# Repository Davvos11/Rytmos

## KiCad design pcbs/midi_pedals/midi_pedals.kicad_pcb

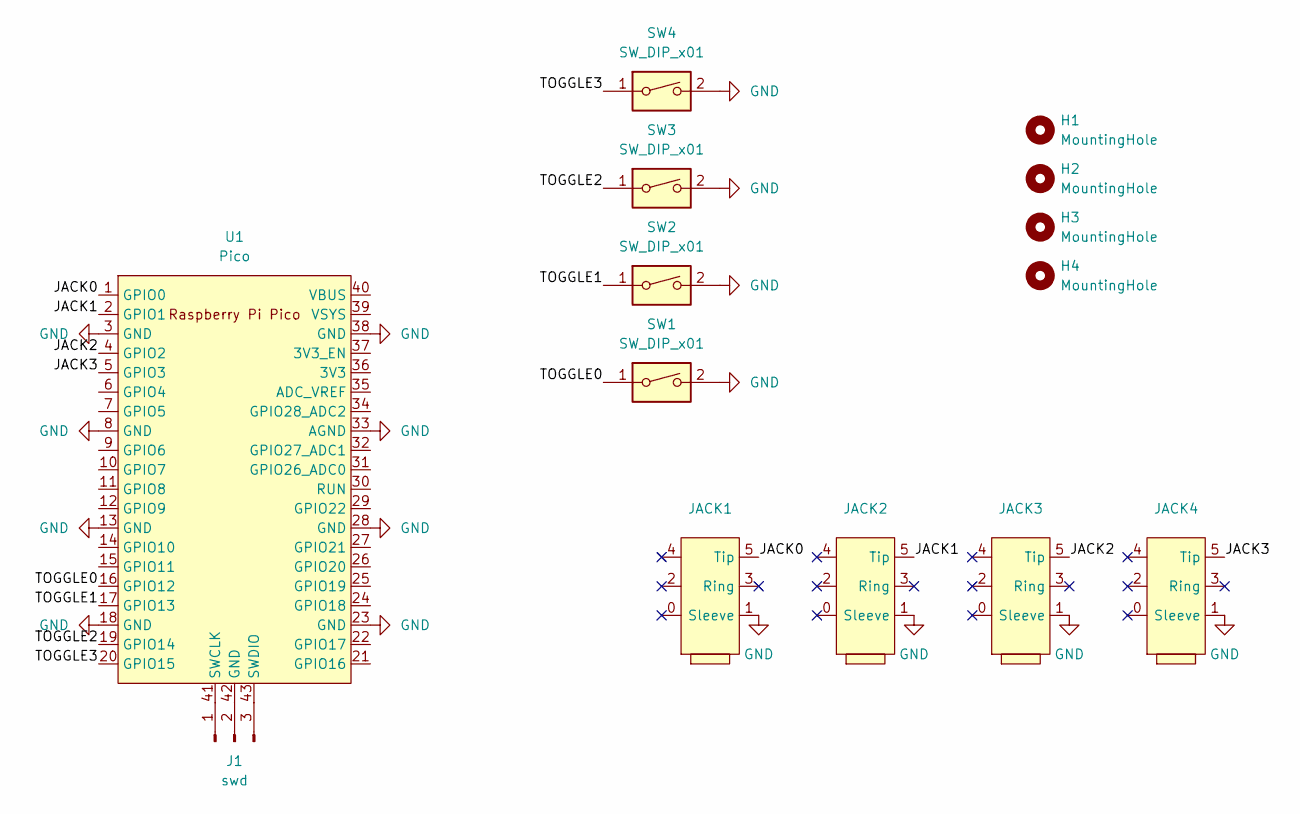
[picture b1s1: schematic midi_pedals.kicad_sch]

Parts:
H1, H2, H3, H4: MountingHole; MountingHole_3.2mm_M3
J1: swd; PinSocket_1x03_P2.54mm_Vertical
JACK1, JACK2, JACK3, JACK4: Jack_6.3mm
SW1, SW2, SW3, SW4: SW_DIP_x01; PinSocket_1x03_P2.54mm_Vertical
U1: Pico; RPi_Pico_SMD_TH

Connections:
/JACK0: JACK1.5 (Tip), U1.1 (GPIO0)
/JACK1: JACK2.5 (Tip), U1.2 (GPIO1)
/JACK2: JACK3.5 (Tip), U1.4 (GPIO2)
/JACK3: JACK4.5 (Tip), U1.5 (GPIO3)
/TOGGLE0: SW1.1, U1.16 (GPIO12)
/TOGGLE1: SW2.1, U1.17 (GPIO13)
/TOGGLE2: SW3.1, U1.19 (GPIO14)
/TOGGLE3: SW4.1, U1.20 (GPIO15)
GND: JACK1.1 (Sleeve), JACK2.1 (Sleeve), JACK3.1 (Sleeve), JACK4.1 (Sleeve), SW1.2, SW2.2, SW3.2, SW4.2, U1.3 (GND), U1.8 (GND), U1.13 (GND), U1.18 (GND), U1.23 (GND), U1.28 (GND), U1.33 (AGND), U1.38 (GND)
unnamed: J1.1, U1.41 (SWCLK)
unnamed: J1.2, U1.42 (GND)
unnamed: J1.3, U1.43 (SWDIO)

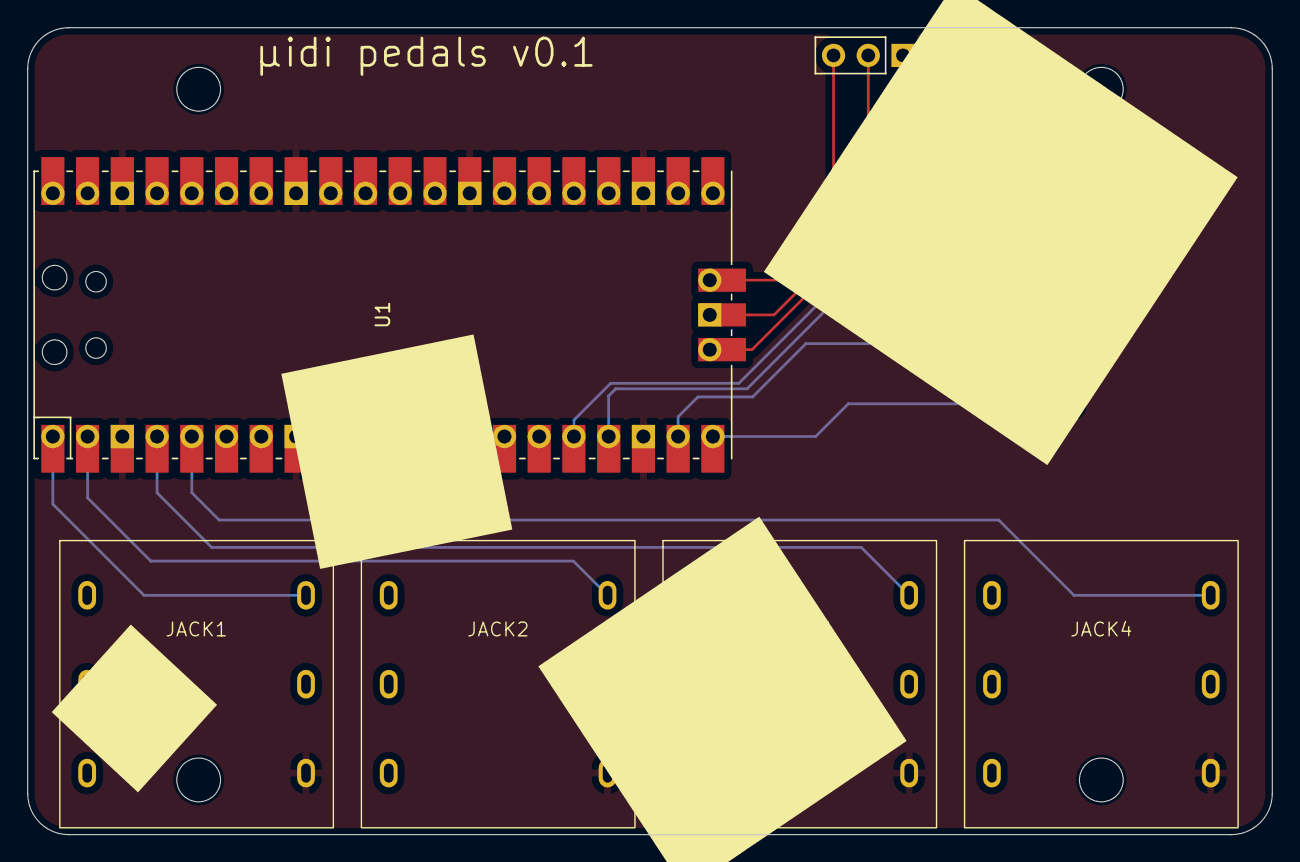
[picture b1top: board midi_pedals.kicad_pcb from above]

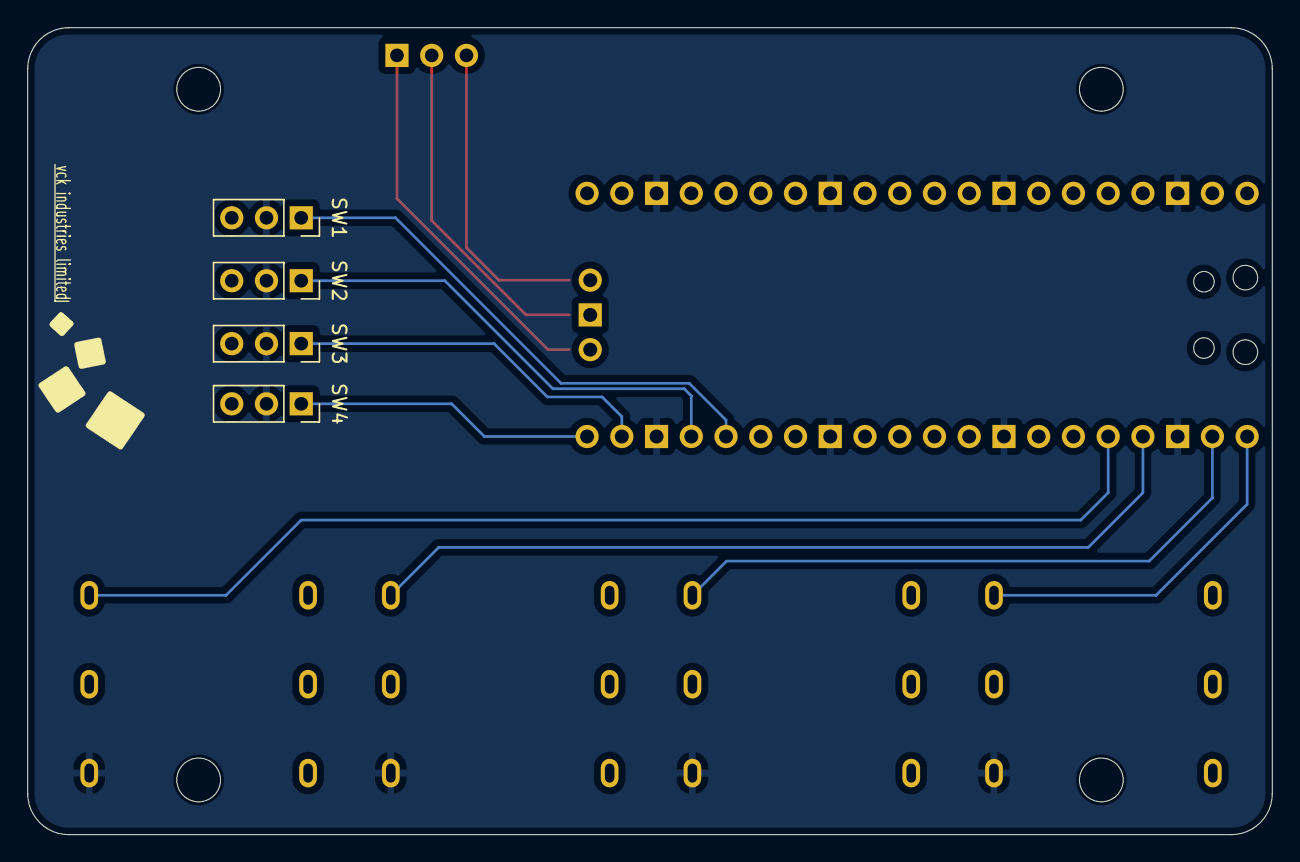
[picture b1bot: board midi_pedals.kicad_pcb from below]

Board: 2 copper layers, 91.0 x 59.0 mm, 14 parts (4 on the bottom side), 12 nets.

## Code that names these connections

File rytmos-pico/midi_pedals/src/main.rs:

#![no_std]
#![no_main]

#[link_section = ".boot2"]
#[no_mangle]
#[used]
pub static BOOT2_FIRMWARE: [u8; 256] = rp2040_boot2::BOOT_LOADER_W25Q080;

use common::debouncer::Debouncer;
use defmt::*;
use defmt_rtt as _;
use embedded_hal::digital::v2::InputPin;
use embedded_hal::digital::v2::OutputPin;
use heapless::Vec;
use itertools::izip;
use panic_probe as _;
use rp_pico::hal::timer::Instant;
use rp_pico::hal::Timer;
use rp_pico::{
    entry,
    hal::{
        clocks::{init_clocks_and_plls, Clock},
        gpio::{self, FunctionSio, Pin, PullUp, SioInput},
        sio::Sio,
        usb::UsbBus,
        Watchdog,
    },
    pac,
};
use usb_device::device::StringDescriptors;
use usb_device::{
    bus::UsbBusAllocator,
    device::{UsbDeviceBuilder, UsbVidPid},
};
use usbd_midi::message::{ControlFunction, U7};
use usbd_midi::CableNumber;
use usbd_midi::Message::ControlChange;
use usbd_midi::{message::Channel, UsbMidiClass};

const PEDALS: usize = 4;
const CC_BANK_A: u8 = 1;
const CC_BANK_B: u8 = 64;

#[entry]
fn main() -> ! {
    let mut pac = pac::Peripherals::take().unwrap();
    let core = pac::CorePeripherals::take().unwrap();
    let sio = Sio::new(pac.SIO);

    let mut watchdog = Watchdog::new(pac.WATCHDOG);
    let clocks = init_clocks_and_plls(
        rp_pico::XOSC_CRYSTAL_FREQ,
        pac.XOSC,
        pac.CLOCKS,
        pac.PLL_SYS,
        pac.PLL_USB,
        &mut pac.RESETS,
        &mut watchdog,
    )
    .ok()
    .unwrap();

    let mut delay = cortex_m::delay::Delay::new(core.SYST, clocks.system_clock.freq().to_Hz());

    let timer = Timer::new(pac.TIMER, &mut pac.RESETS, &clocks);

    let pins = gpio::Pins::new(
        pac.IO_BANK0,
        pac.PADS_BANK0,
        sio.gpio_bank0,
        &mut pac.RESETS,
    );

    info!("Creating usb devices.");

    let usb_bus = UsbBusAllocator::new(UsbBus::new(
        pac.USBCTRL_REGS,
        pac.USBCTRL_DPRAM,
        clocks.usb_clock,
        true,
        &mut pac.RESETS,
    ));

    let mut led_pin = pins.gpio25.into_push_pull_output();

    let pedal_pins: [Pin<_, FunctionSio<SioInput>, PullUp>; PEDALS] = [
        pins.gpio0.reconfigure().into_dyn_pin(),
        pins.gpio1.reconfigure().into_dyn_pin(),
        pins.gpio2.reconfigure().into_dyn_pin(),
        pins.gpio3.reconfigure().into_dyn_pin(),
    ];
    let mut pedal_debouncers: Vec<_, PEDALS> =
        pedal_pins.iter().map(|_| Debouncer::new(1000)).collect();

    let switch1: Pin<_, FunctionSio<SioInput>, PullUp> = pins.gpio12.reconfigure();
    let switch2: Pin<_, FunctionSio<SioInput>, PullUp> = pins.gpio13.reconfigure();
    let mut switch1_deb = Debouncer::new(1000);
    let mut switch2_deb = Debouncer::new(1000);

    let control_changes_a = create_ccs(CC_BANK_A);
    let control_changes_b = create_ccs(CC_BANK_B);

    led_pin.set_high().unwrap();

    let mut midi = UsbMidiClass::new(&usb_bus, 1, 0).unwrap();

    let mut usb_dev = UsbDeviceBuilder::new(&usb_bus, UsbVidPid(0xabc9, 0xee0))
        .device_class(0)
        .device_sub_class(0)
        .strings(&[StringDescriptors::default()
            .manufacturer("de vck")
            .product("midi pedals lmao")
            .serial_number("0")])
        .unwrap()
        .build();

    info!("usb device is created");

    let mut control_changes = if switch1.is_high().unwrap() {
        info!(
            "Starting using bank A (switch 1: {})",
            switch1.is_high().unwrap()
        );
        &control_changes_a
    } else {
        info!(
            "Starting using bank B (switch 1: {})",
            switch1.is_high().unwrap()
        );
        &control_changes_b
    };
    let mut double_cancellation = switch2.is_high().unwrap();
    info!(
        "Starting with double-press cancellation = {}",
        double_cancellation
    );
    // Create counters for each pedal (0: last time pedal up, 1: last time pedal down)
    let mut last_presses: Vec<_, PEDALS> =
        pedal_pins.iter().map(|_| (Instant::from_ticks(0), Instant::from_ticks(0))).collect();
    let mut pressed = pedal_pins.iter().filter(|p| p.is_high().unwrap()).count();

    loop {
        // Poll USB device to keep connection alive
        usb_dev.poll(&mut [&mut midi]);

        switch1_deb.update(switch1.is_high().unwrap());
        switch2_deb.update(switch2.is_high().unwrap());

        // Determine the CC values based on the switch setting
        if switch1_deb.stable_rising_edge() {
            debug!("Switching to bank A");
            // Send pedal off to all B channels (when switching)
            for cc in &control_changes_b {
                send_midi_cc(&mut midi, cc, U7::MIN).ok();
                delay.delay_ms(1);
            }
            // Set current channels to A
            control_changes = &control_changes_a;
        } else if switch1_deb.stable_falling_edge() {
            debug!("Switching to bank B");
            for cc in &control_changes_a {
                send_midi_cc(&mut midi, cc, U7::MIN).ok();
                delay.delay_ms(1);
            }
            // Set current channels to B
            control_changes = &control_changes_b;
        }

        // Determine if we double-press-cancellation is enabled
        if switch2_deb.stable_rising_edge() {
            debug!("Enabling double-press cancellation");
            double_cancellation = true;
        } else if switch2_deb.stable_falling_edge() {
            debug!("Disabling double-press cancellation");
            double_cancellation = false;
        }

        for (pin, debouncer, cc, last_pressed) in izip!(
            &pedal_pins,
            &mut pedal_debouncers,
            control_changes,
            &mut last_presses
        ) {
            debouncer.update(pin.is_high().unwrap());
            let mut up = false;
            let mut down = false;

            if debouncer.stable_falling_edge() {
                down = true;
                debug!("{} down (MIDI {})", pin.id().num, u8::from(cc.0.clone()));
                pressed += 1;
            }

            if debouncer.stable_rising_edge() {
                up = true;
                debug!("{} up (MIDI {})", pin.id().num, u8::from(cc.0.clone()));
                pressed = pressed.saturating_sub(1);
            }
            
            if up || down {
                // Determine time since last up or down event and determine if we should cancel
                let elapsed = if up {
                    timer.get_counter().checked_duration_since(last_pressed.0)
                } else {
                    timer.get_counter().checked_duration_since(last_pressed.1)
                };
                let should_cancel = elapsed.map(|e| e.to_millis() <= 500).unwrap_or(false);
                if double_cancellation && should_cancel {
                    debug!("Cancelled sending midi ({:?} ms since last press)", elapsed.map(|e| e.to_millis()));
                }
                // Send MIDI signal (or cancel)
                if !double_cancellation || !should_cancel {
                    let value = if up {U7::MIN} else {U7::MAX};
                    send_midi_cc(&mut midi, cc, value).ok();
                }
                // Update timers
                if up {
                    last_pressed.0 = timer.get_counter();
                } else {
                    last_pressed.1 = timer.get_counter();
                }
            }
        }

        if pressed > 0 {
            led_pin.set_low().ok();
        } else {
            led_pin.set_high().ok();
        }
    }
}

fn send_midi_cc(
    midi: &mut UsbMidiClass<UsbBus>,
    cc: &ControlFunction,
    value: U7,
) -> usb_device::Result<usize> {
    midi.send_packet(
        ControlChange(Channel::Channel1, cc.clone(), value).into_packet(CableNumber::Cable0),
    )
}

fn create_ccs(offset: u8) -> Vec<ControlFunction, PEDALS> {
    (0..PEDALS as u8)
        .map(|i| ControlFunction((i + offset).try_into().unwrap()))
        .collect()
}

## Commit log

2025-04-18 Send proper pedal cc and add multiple pedal support
2025-04-18 Add switch for switching between banks of CCs
2025-04-18 Add LED status based on pedals
2025-04-29 Change from 2 to 4 pedal inputs
2025-05-02 Fix pin numbering
2025-05-02 Fix switch 1 having the incorrect initial value
2025-05-02 Add tooling setup to README
2025-05-02 Add double-press cancellation feature to midi-pedals
2025-05-02 Add safe subtraction for LED status for midi-pedals
